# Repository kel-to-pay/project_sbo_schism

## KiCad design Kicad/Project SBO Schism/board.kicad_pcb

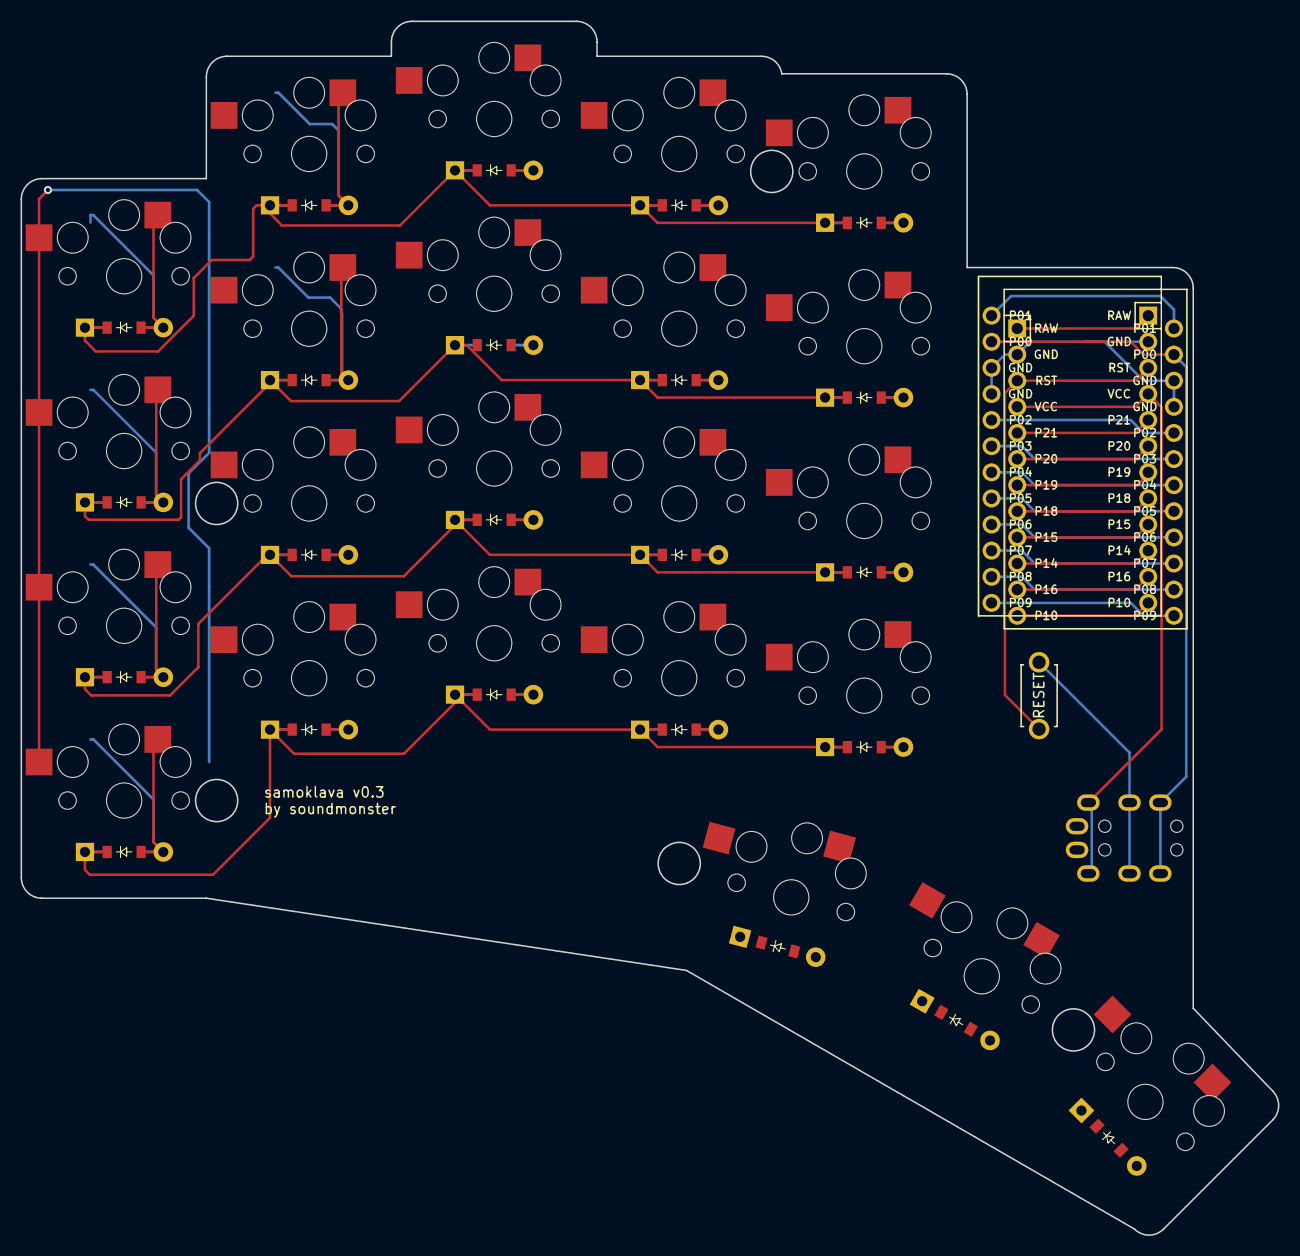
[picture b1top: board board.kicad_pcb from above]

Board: 2 copper layers, 122.3 x 118.1 mm, 50 parts (0 on the bottom side), 45 nets.

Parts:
B1: ResetSW
D1, D2, D3, D4, D5, D6, D7, D8, D9, D10, D11, D12, D13, D14, D15, D16, D17, D18, D19, D20, D21, D22, D23: ComboDiode
MCU1, MCU2: ProMicro
S1, S2, S3, S4, S5, S6, S7, S8, S9, S10, S11, S12, S13, S14, S15, S16, S17, S18, S19, S20, S21, S22, S23: PG1350
TRRS1: TRRS-PJ-320A-dual

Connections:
GND: B1.2, MCU1.2, MCU1.15, MCU1.16, MCU2.2, MCU2.15, MCU2.16, TRRS1.3
P0: MCU1.14, MCU2.14, TRRS1.4
P1: MCU1.13, MCU2.13
P2: MCU1.17, MCU2.17
P3: MCU1.18, MCU2.18
P9: MCU1.24, MCU2.24
P10: MCU1.12, MCU2.12
P16: MCU1.11, MCU2.11
P21: MCU1.5, MCU2.5
RAW: MCU1.1, MCU2.1
RST: B1.1, MCU1.3, MCU2.3
VCC: MCU1.4, MCU2.4, TRRS1.2
col_index: MCU1.9, MCU2.9, S13.2, S14.2, S15.2, S16.2, S22.2
col_inner: MCU1.10, MCU2.10, S17.2, S18.2, S19.2, S20.2, S23.2
col_middle: MCU1.8, MCU2.8, S9.2, S10.2, S11.2, S12.2, S21.2
col_pinky: MCU1.6, MCU2.6, S1.2, S2.2, S3.2, S4.2
col_ring: MCU1.7, MCU2.7, S5.2, S6.2, S7.2, S8.2
far_thumb: D23.2, S23.1
home_thumb: D22.2, S22.1
index_bottom: D13.2, S13.1
index_extra: D16.2, S16.1
index_home: D14.2, S14.1
index_top: D15.2, S15.1
inner_bottom: D17.2, S17.1
inner_extra: D20.2, S20.1
inner_home: D18.2, S18.1
inner_top: D19.2, S19.1
middle_bottom: D9.2, S9.1
middle_extra: D12.2, S12.1
middle_home: D10.2, S10.1
middle_top: D11.2, S11.1
near_thumb: D21.2, S21.1
pinky_bottom: D1.2, S1.1
pinky_extra: D4.2, S4.1
pinky_home: D2.2, S2.1
pinky_top: D3.2, S3.1
ring_bottom: D5.2, S5.1
ring_extra: D8.2, S8.1
ring_home: D6.2, S6.1
ring_top: D7.2, S7.1
row_bottom: D1.1, D5.1, D9.1, D13.1, D17.1, MCU1.21, MCU2.21
row_extra: D4.1, D8.1, D12.1, D16.1, D20.1, MCU1.23, MCU2.23
row_home: D2.1, D6.1, D10.1, D14.1, D18.1, MCU1.20, MCU2.20
row_thumb: D21.1, D22.1, D23.1, MCU1.22, MCU2.22
row_top: D3.1, D7.1, D11.1, D15.1, D19.1, MCU1.19, MCU2.19

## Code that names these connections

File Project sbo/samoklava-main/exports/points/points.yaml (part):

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        autobind: 10
        skip: false
        asym: both
        colrow: pinky_bottom
        name: matrix_pinky_bottom
        footprints:
            choc_hotswap:
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                    shift:
                        - 0
                        - -5
        column_net: col_pinky
        row_net: row_bottom
        zone: &ref_1
            key:
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                    key:
                        stagger: 0 ky
                        spread: kx
                        column_net: col_pinky
                    rows: {}
                    name: pinky
                ring: &ref_2
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        autobind: 10
        skip: false
        asym: both
        colrow: pinky_home
        name: matrix_pinky_home
        footprints:
            choc_hotswap:
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                    shift:
                        - 0
                        - -5
        column_net: col_pinky
        row_net: row_home
        zone: *ref_1
        col: *ref_0
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        autobind: 10
        skip: false
        asym: both
        colrow: pinky_top
        name: matrix_pinky_top
        footprints:
            choc_hotswap:
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                    shift:
                        - 0
                        - -5
        column_net: col_pinky
        row_net: row_top
        zone: *ref_1
        col: *ref_0
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        autobind: 10
        skip: false
        asym: both
        colrow: pinky_extra
        name: matrix_pinky_extra
        footprints:
            choc_hotswap:
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                    shift:
                        - 0
                        - -5
        column_net: col_pinky
        row_net: row_extra
        zone: *ref_1
        col: *ref_0
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
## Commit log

2024-05-27 Wrong folder uploaded
2024-05-27 begin wiring
2024-05-27 the beginning of the wiring
    must be neat must be neat must be neat must be neat must be neat must be neat
2024-05-28 Work continues
2024-06-04 well
